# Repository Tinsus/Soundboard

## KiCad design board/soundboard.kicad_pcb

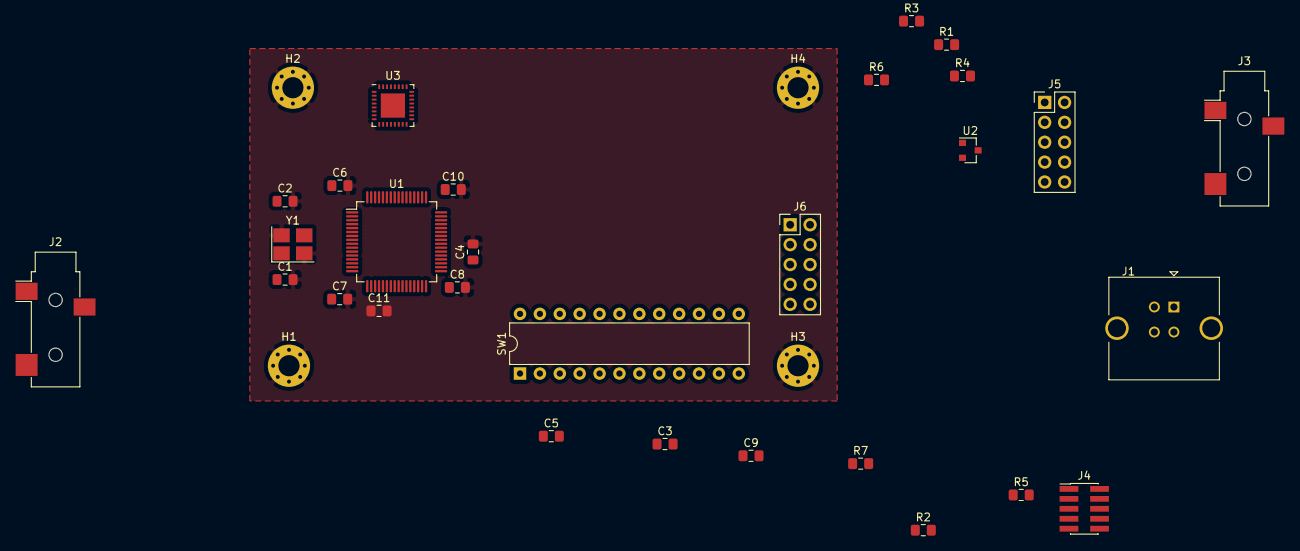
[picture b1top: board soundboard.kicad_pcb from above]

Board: 2 copper layers, 33 parts (0 on the bottom side), 27 nets, no tracks yet.

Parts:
C1, C2: 12pF; C_0805_2012Metric_Pad1.15x1.40mm_HandSolder
C3, C4, C6, C7, C9, C10, C11: 100nF; C_0805_2012Metric_Pad1.15x1.40mm_HandSolder
C5, C8: 1µF; C_0805_2012Metric_Pad1.15x1.40mm_HandSolder
H1, H2, H3, H4: MountingHole_Pad; MountingHole_2.7mm_M2.5_Pad_Via
J1: USB_B; USB_B_Amphenol_MUSB-D511_Vertical_Rugged
J2, J3: AudioJack3; Jack_3.5mm_CUI_SJ-3523-SMT_Horizontal
J4: SWD; PinHeader_2x05_P1.27mm_Vertical_SMD
J5: Input Matrix; PinHeader_2x05_P2.54mm_Vertical
J6: Output Matrix; PinHeader_2x05_P2.54mm_Vertical
R1, R2, R3, R4, R5, R6, R7: 10k; R_0805_2012Metric_Pad1.15x1.40mm_HandSolder
SW1: DIP_CFG; DIP-24_W7.62mm
U1: STM32F303RETx; LQFP-64_10x10mm_P0.5mm
U2: XC6206P332MR; SOT-23
U3: PCM6260xxxxxx; WQFN-32-1EP_5x5mm_P0.5mm_EP3.1x3.1mm
Y1: Crystal_GND24; Crystal_SMD_3225-4Pin_3.2x2.5mm_HandSoldering

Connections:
+3V3: C4.1, C6.1, C7.1, C8.1, C9.1, C10.1, C11.1, J4.1, U1.1, U1.13, U1.19, U1.32, U1.48, U1.64, U2.2
+5V: C5.1, J1.1, U2.3
/MAT_DIP_0: R6.2, SW1.19, SW1.20, SW1.21, SW1.22, SW1.23, SW1.24, U1.39
/MAT_DIP_1: R7.2, SW1.13, SW1.14, SW1.15, SW1.16, SW1.17, SW1.18, U1.38
/MAT_IN_0: J5.7, R2.2, U1.8
/MAT_IN_1: J5.8, R3.2, U1.9
/MAT_IN_2: J5.9, R4.2, U1.10
/MAT_IN_3: J5.10, R5.2, U1.11
/MAT_OUT_A0: J6.7, U1.20
/MAT_OUT_A1: J6.8, U1.21
/MAT_OUT_A2: J6.9, U1.22
/MAT_OUT_A3: J6.10, U1.23
/MAT_OUT_B0: J5.1, J6.1, SW1.1, SW1.7, U1.24
/MAT_OUT_B1: J5.2, J6.2, SW1.2, SW1.8, U1.25
/MAT_OUT_B2: J5.3, J6.3, SW1.3, SW1.9, U1.26
/MAT_OUT_B3: J5.4, J6.4, SW1.4, SW1.10, U1.27
/MAT_OUT_B4: J5.5, J6.5, SW1.5, SW1.11, U1.28
/MAT_OUT_B5: J5.6, J6.6, SW1.6, SW1.12, U1.29
/NRST: C3.1, J4.10, U1.7
/SWDIO: J4.2, U1.46
/SWO: J4.6, U1.55
/USB+: J1.3, U1.45
/USB-: J1.2, U1.44
GND: C1.2, C2.2, C3.2, C4.2, C5.2, C6.2, C7.2, C8.2, C9.2, C10.2, C11.2, H1.1, H2.1, H3.1, H4.1, J1.4, J1.5, J2.R, J2.S, J3.S, J4.3, J4.5, J4.9, R1.2, R2.1, R3.1, R4.1, R5.1, R6.1, R7.1, U1.12, U1.18, U1.31, U1.47, U1.63, U2.1, U3.8, U3.33, Y1.2, Y1.4
unnamed: C1.1, U1.5, Y1.1
unnamed: C2.1, U1.6, Y1.3
unnamed: R1.1, U1.60

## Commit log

2020-10-16 Add board to repo
2020-10-16 Fix library path
2020-10-16 Update schematic foo
2020-10-16 Move ADC to analog sheet
2020-10-18 ADC circuit and I2C address jumper config
2020-10-18 added boost osc, added output voltage stabilize cap, added recording lines
2020-10-19 capacitor highpass values for 44kHz sampling rate on record ic input
2020-10-22 hirarchical pins
2020-10-22 better audio port
2020-10-22 Soundboard STM32 CubeMX Config file
2020-10-22 keep pinout setting
2020-10-22 Swap stm32 for larger one
2020-10-22 exposed names
2020-10-22 Add DAC chip
2020-10-22 Add Display connector
2020-10-22 audio playback IC
2020-10-22 added playback pins
2020-10-22 use ? as name
2020-10-22 Connect analog part to microcontroller
2020-10-22 Add Connectors for displays
2020-10-22 analog sheet audio playback lines
2020-10-22 soundboard I2C pins
2020-10-23 Change analog sheet outer foo
2020-10-23 analog playback
2020-10-23 Added Mixing Subsheet
2020-10-24 audio amp circuit
